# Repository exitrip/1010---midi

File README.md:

# 1010---midi
Trying organize an otherwise un-organized repo for public consumption:

## Overview
This repo contains everything one needs to repurpose an "iTrip 1G Nano" as a generic radio transmitter, including an adaptor circuit board to simplify the hack, and a "headless" Arduino program to flash firmware on to the iTrip's LPC936 microcontroller.

See the `kicad` directory for a partial schematic of the iTrip and the complete schematic and layout of the adaptor PCB.  I've got lots of the PCBs, so please ask me to send you some instead of making your own for now.

### Required supplies
If you want to replicate this work you'll need:
- iTrips (again ask me for some, I've got hundreds).  It's good to have plenty of extras for a workshop.
- an Arduino and homemade programming cable
- Soldering equipment, wire cutters, a small screw driver helps, etc.
- ~1m electrical wire per transmitter
- to pick a power source for the iTrip:
  - 2x AA/AAA battery pack, try finding them from surplus sites like [Goldmine Electronics](https://theelectronicgoldmine.com/products/g27885?_pos=18&_sid=e9574ebc7&_ss=r)
  - TO-92 or SOT23-5 3.3V, 100mA regulator (e.g. [L78L33ACZ](https://www.digikey.com/en/products/detail/stmicroelectronics/L78L33ACZ/1038304))
  - or the [FTDI FT232RL](https://www.digikey.com/en/products/detail/ftdi-future-technology-devices-international-ltd/FT232RL-REEL/1836385)  USB-to-UART converter with onboard regulator.  This chip is relatively fine pitch SMT TSSOP, so it will be challenging to seat without the right soldering tools and experience.  

A quick note about the FTDI chip:  Seating this chip will allow you to send and recieve MIDI (via serial) commands to the transmitter over USB, in fact each FTDI chip can drive up to 8 transmitters, but there are undocumented details as to how to set this up.  All of the PurrData patches, touchOSC setup, and most of the uVision code target custom modular hardware that is also poorly documented and out of scope of a workshop.  Even without the "onboard" FTDI, you can access all this functionality by using any [3.3V USB-Serial cable](https://www.adafruit.com/product/70) hooked up to the TX/RX on the adpator PCB. Reach out, I happy to discuss further.

Another note about firmware:  The LPC936 firmware programmed by the Arduino is stored in the Arduino firmware directly.  Recompiling new firmware unfortunately requires a licensed copy of KEIL uVision Cx51, which is thousands of dollars last I checked.  The "free" versions of uVision have a prohibitively small size limit, and cannot build the code as is.  I'm still investigating if I can strip the project enough...

### Setting up the programmer
See [README](arduino/exitrip_flash_programmer/README.md) in arduino folder.

## Steps for the hack
- Open up the iTrip.  Easiest way is to slip a flat head above the button and pry the plastic case open like an oyster.  Be a bit careful with the button though.
- Don't put too much stress on the cables inside the now opened iTrip, they can easily break off the PCB.
- Break the connectors from the front plastic shell.  This takes some practice, and there's maybe half a dozen ways to do this.  Notice that there's a seam in the front plastic around connectors, just under the FCC ID number.  Pressing the smaller plastic piece out of the front cover is easy, most of the time.  You can also just cut the front cover up too.
- Cut loose the antenna (black wire soldered, ANT2, to the board closest to the USB port, J3) and push the wire loose out the back of the black plastic

- Solder ~1m of wire to the antenna, this is now a [1/4 whip antenna](https://en.wikipedia.org/wiki/Whip_antenna) at ~75MHz. It's good to cheat it shorter than 1m, as that tunes it up the FM spectrum, but don't go longer.
- Connect the programming cable to the iTrip and Arduino.  Make sure the external power supply PCB is DISCONNECTED from the iTrip to be programmed.
- Power on or RESET the Arduino.  At boot up it will blink slowly, but when it successfully handshakes with the LPC936, the LED will start blinking faster during programming.  Wait until the LED is blinking slow again, which indicates programming is complete.  This is a good time to test the iTrip without the added power supply, as it will recieve power from the Arduino programmer directly.  The iTrip itself is working and correctly programmed if:
  - The red LED in the corner comes on solid 
  - The red LED turns on and off with a middle button press (this turns the transmitter on and off)
  - While the LED is on there's a signal (silence) on 87.9 MHz (every time the iTrip boots up the transmission freqency is reset to 87.9)
  - Pressing the up and down buttons, tunes the transmitter up and down.
- This step can be done at anytime, but once you've tested the iTrip works while connected to the Arduino, you can be sure that further problems are caused by the power supply.
  - Solder the desired power supply to the adaptor PCB (e.g. GND to battery negative, 3.3V to battery positive).  Any of the ICs will take 5V from either the 5V header on the adaptor or the USB port on the iTrip.  A useful 5V and 3.3V will come OUT of those headers too!

  ## Suggestions about workshops
  - FM radios are not as common as they used to be.  BRING SOME, otherwise there's a big sad trombone at the end of the build
  - Have an SDR reciever setup on a laptop to visualize the transmissions.  It will also double as a reciever.  These turnkey [RTL-SDR kits](https://www.rtl-sdr.com/buy-rtl-sdr-dvb-t-dongles/) are awesome for the price.

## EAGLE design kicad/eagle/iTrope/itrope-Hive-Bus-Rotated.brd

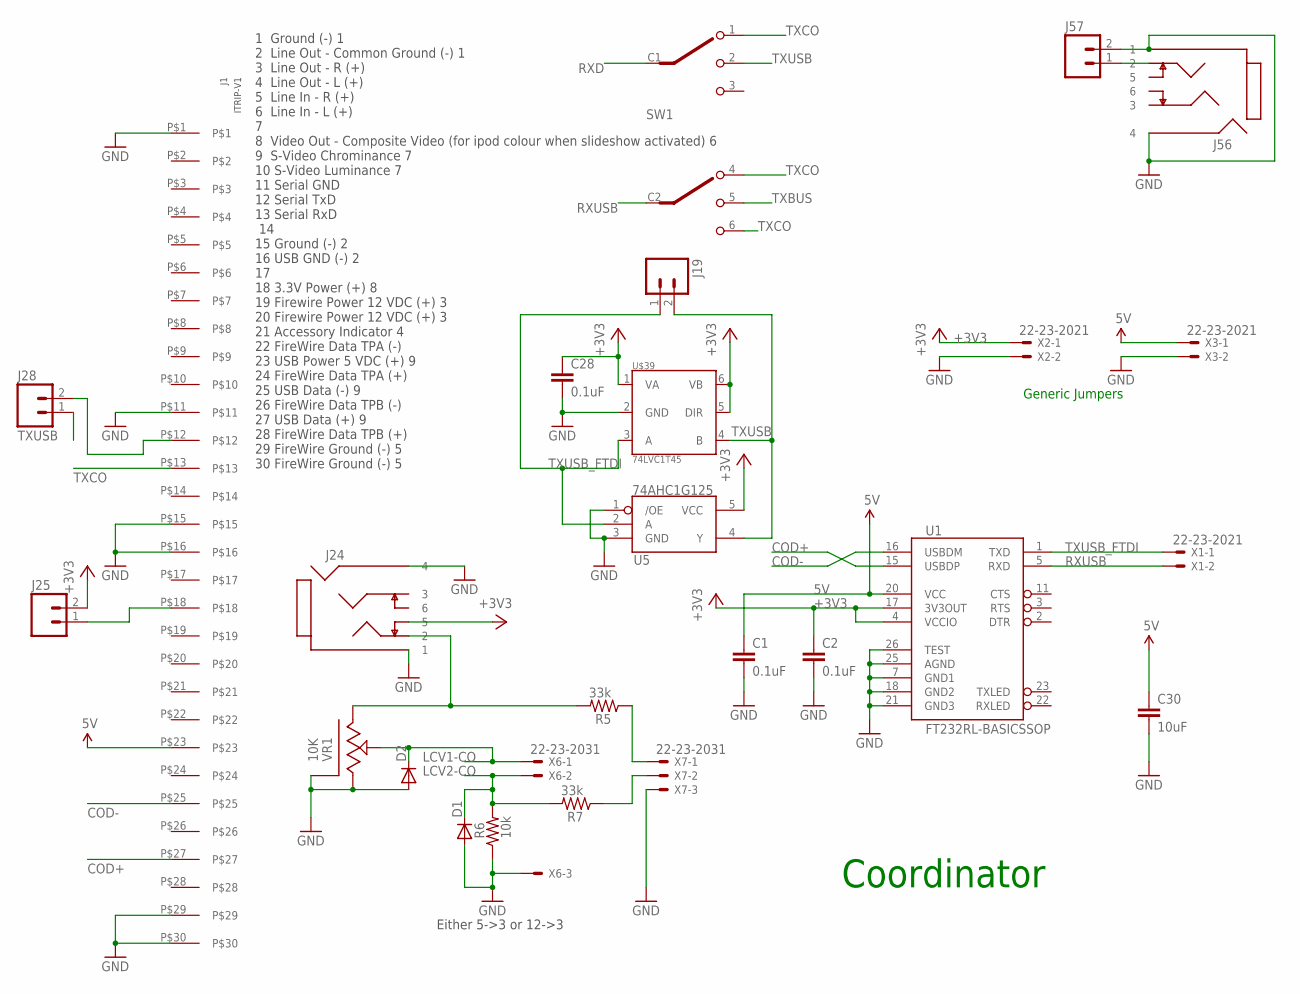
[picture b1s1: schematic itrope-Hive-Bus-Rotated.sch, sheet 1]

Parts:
C1, C2, C28: 0.1uF; CAP-0603
C30: 10uF; CAP-0805
D1, D2: DIODESOD; SOD-323
J1: ITRIP-V1; 30PINEDGE+ITRIP
J19, J25, J28, J57: HDR-2H02-PTH; H02-PTH
J24, J56: JACK-PHONO-4COND-SW; CUI-SJ-4351
R5, R7: 33k; C0402
R6: 10k; C0402
SW1: SWITCH-SLIDE-DP3TAYZ0203; SWITCH-CK-AYZ0203
U1: FT232RL-BASICSSOP; SSOP28DB
U5: 74AHC1G125; SOT23-5
U$39: 74LVC1T45; SC70-6
VR1: 10K; POT-SLIDE-30MM
X1, X2, X3: 22-23-2021
X6, X7: 22-23-2031

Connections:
5V: C1.1, C30.1, J1.P$23, U1.20 (VCC), X3.1; also elsewhere on the board
+3V3: C2.1, C28.1, J24.5, J25.2, U1.4 (VCCIO), U1.17 (3V3OUT), U5.5 (VCC), U$39.1 (VA), U$39.5 (DIR), U$39.6 (VB), X2.1; also elsewhere on the board
COD+: J1.P$27, U1.15 (USBDP)
COD-: J1.P$25, U1.16 (USBDM)
GND: C1.2, C2.2, C28.2, C30.2, D1.2 (A), D2.2 (A), J1.P$1, J1.P$11, J1.P$15, J1.P$16, J1.P$29, J1.P$30, J24.1, J24.4, J56.1, J56.4, J57.2, R6.1, U1.7 (GND1), U1.18 (GND2), U1.21 (GND3), U1.25 (AGND), U1.26 (TEST), U5.1 (/OE), U5.3 (GND), U$39.2 (GND), VR1.3, VR1.P$4 (CASE), VR1.P$5 (CASE), VR1.P$6 (CASE), VR1.P$7 (CASE), X2.2, X3.2, X6.3, X7.3; also elsewhere on the board
LCV1-CO: D2.1 (C), VR1.2, X6.1
LCV2-CO: D1.1 (C), R6.2, R7.2, X6.2
unnamed: R7.1, X7.2
unnamed: R5.1, X7.1
unnamed: J1.P$18, J25.1
unnamed: J24.2, R5.2, VR1.1
unnamed: J1.P$12, J28.2
unnamed: J56.2, J57.1
RXD: SW1.C1; also elsewhere on the board
RXUSB: SW1.C2, U1.5 (RXD), X1.2
TXBUS: SW1.5; also elsewhere on the board
TXCO: J1.P$13, SW1.1, SW1.4, SW1.6
TXUSB: J19.2, J28.1, SW1.2, U5.4 (Y), U$39.4 (B)
TXUSB_FTDI: J19.1, U1.1 (TXD), U5.2 (A), U$39.3 (A), X1.1

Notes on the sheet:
1 Ground (-) 1 2 Line Out - Common Ground (-) 1 3 Line Out - R (+) 4 Line Out - L (+) 5 Line In - R (+) 6 Line In - L (+) 7 8 Video Out - Composite Video (for ipod colour when slideshow activated) 6 9 S-Video Chrominance 7 10 S-Video Luminance 7 11 Serial GND 12 Serial TxD 13 Serial RxD 14 15 Groun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
Either 5->3 or 12->3
Generic Jumpers
Coordinator

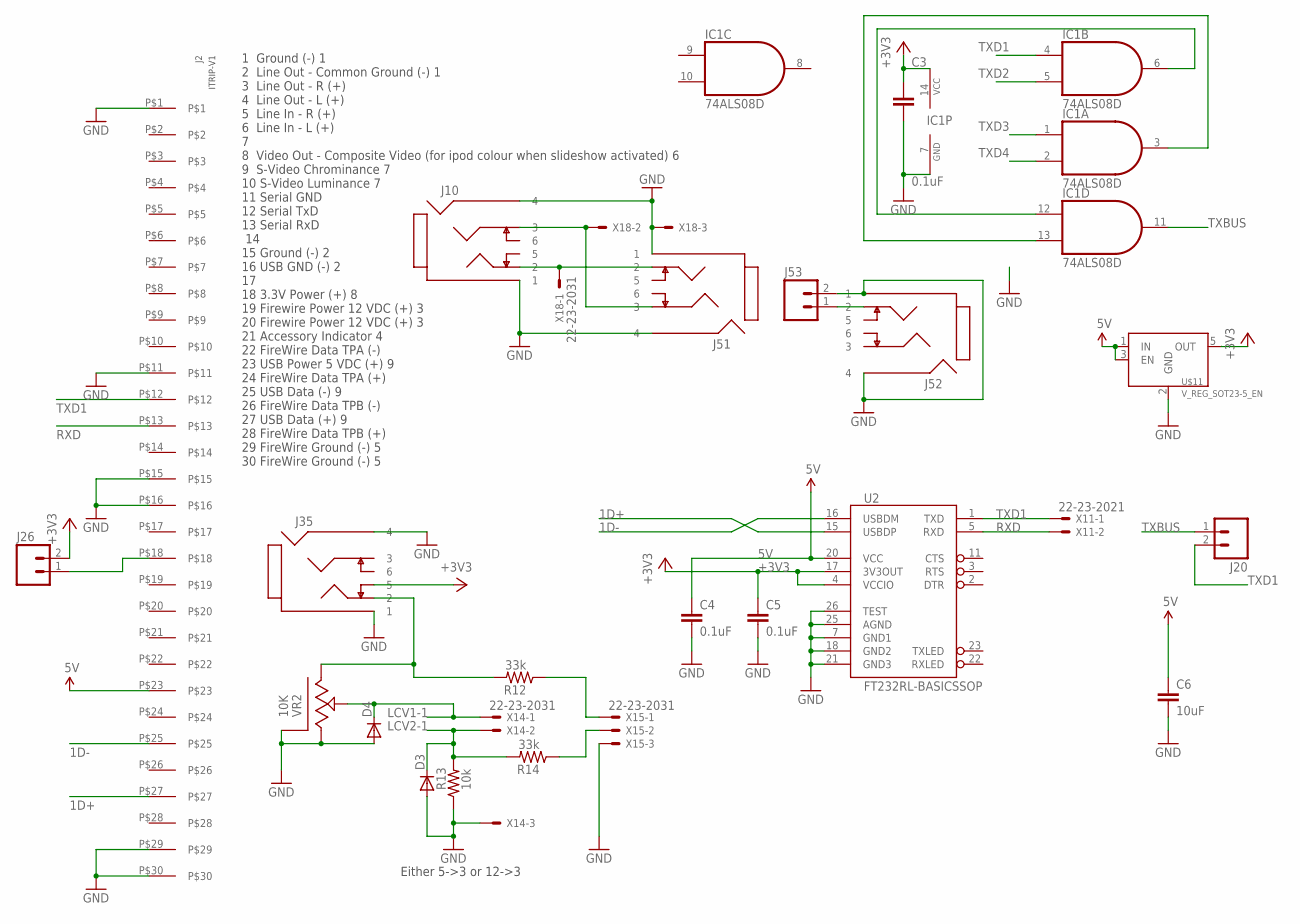
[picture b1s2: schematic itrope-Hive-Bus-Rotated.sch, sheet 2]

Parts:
C3, C4, C5: 0.1uF; CAP-0603
C6: 10uF; CAP-0805
D3, D4: DIODESOD; SOD-323
IC1: 74ALS08D; SO14
J2: ITRIP-V1; 30PINEDGE+ITRIP
J10, J35, J51, J52: JACK-PHONO-4COND-SW; CUI-SJ-4351
J20, J26, J53: HDR-2H02-PTH; H02-PTH
R12, R14: 33k; C0402
R13: 10k; C0402
U2: FT232RL-BASICSSOP; SSOP28DB
U$11: V_REG_SOT23-5_EN; SOT23-5
VR2: 10K; POT-SLIDE-30MM
X11: 22-23-2021
X14, X15, X18: 22-23-2031

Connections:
1D+: J2.P$27, U2.15 (USBDP)
1D-: J2.P$25, U2.16 (USBDM)
5V: C4.1, C6.1, J2.P$23, U2.20 (VCC), U$11.1 (IN), U$11.3 (EN); also elsewhere on the board
+3V3: C3.1, C5.1, IC1.14 (VCC), J26.2, J35.5, U2.4 (VCCIO), U2.17 (3V3OUT), U$11.5 (OUT); also elsewhere on the board
GND: C3.2, C4.2, C5.2, C6.2, D3.2 (A), D4.2 (A), IC1.7 (GND), J2.P$1, J2.P$11, J2.P$15, J2.P$16, J2.P$29, J2.P$30, J10.1, J10.4, J35.1, J35.4, J51.1, J51.4, J52.1, J52.4, J53.2, R13.1, U2.7 (GND1), U2.18 (GND2), U2.21 (GND3), U2.25 (AGND), U2.26 (TEST), U$11.2 (GND), VR2.3, VR2.P$4 (CASE), VR2.P$5 (CASE), VR2.P$6 (CASE), VR2.P$7 (CASE), X14.3, X15.3, X18.3; also elsewhere on the board
LCV1-1: D4.1 (C), VR2.2, X14.1
LCV2-1: D3.1 (C), R13.2, R14.2, X14.2
unnamed: R14.1, X15.2
unnamed: R12.1, X15.1
unnamed: J2.P$18, J26.1
unnamed: IC1.6 (O), IC1.12 (I0)
unnamed: IC1.3 (O), IC1.13 (I1)
unnamed: J35.2, R12.2, VR2.1
unnamed: J10.2, J51.2, X18.1
unnamed: J10.3, J51.3, X18.2
unnamed: J52.2, J53.1
RXD: J2.P$13, U2.5 (RXD), X11.2; also elsewhere on the board
TXBUS: IC1.11 (O), J20.1; also elsewhere on the board
TXD1: IC1.4 (I0), J2.P$12, J20.2, U2.1 (TXD), X11.1; also elsewhere on the board
TXD2: IC1.5 (I1); also elsewhere on the board
TXD3: IC1.1 (I0); also elsewhere on the board
TXD4: IC1.2 (I1); also elsewhere on the board

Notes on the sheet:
1 Ground (-) 1 2 Line Out - Common Ground (-) 1 3 Line Out - R (+) 4 Line Out - L (+) 5 Line In - R (+) 6 Line In - L (+) 7 8 Video Out - Composite Video (for ipod colour when slideshow activated) 6 9 S-Video Chrominance 7 10 S-Video Luminance 7 11 Serial GND 12 Serial TxD 13 Serial RxD 14 15 Groun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
Either 5->3 or 12->3

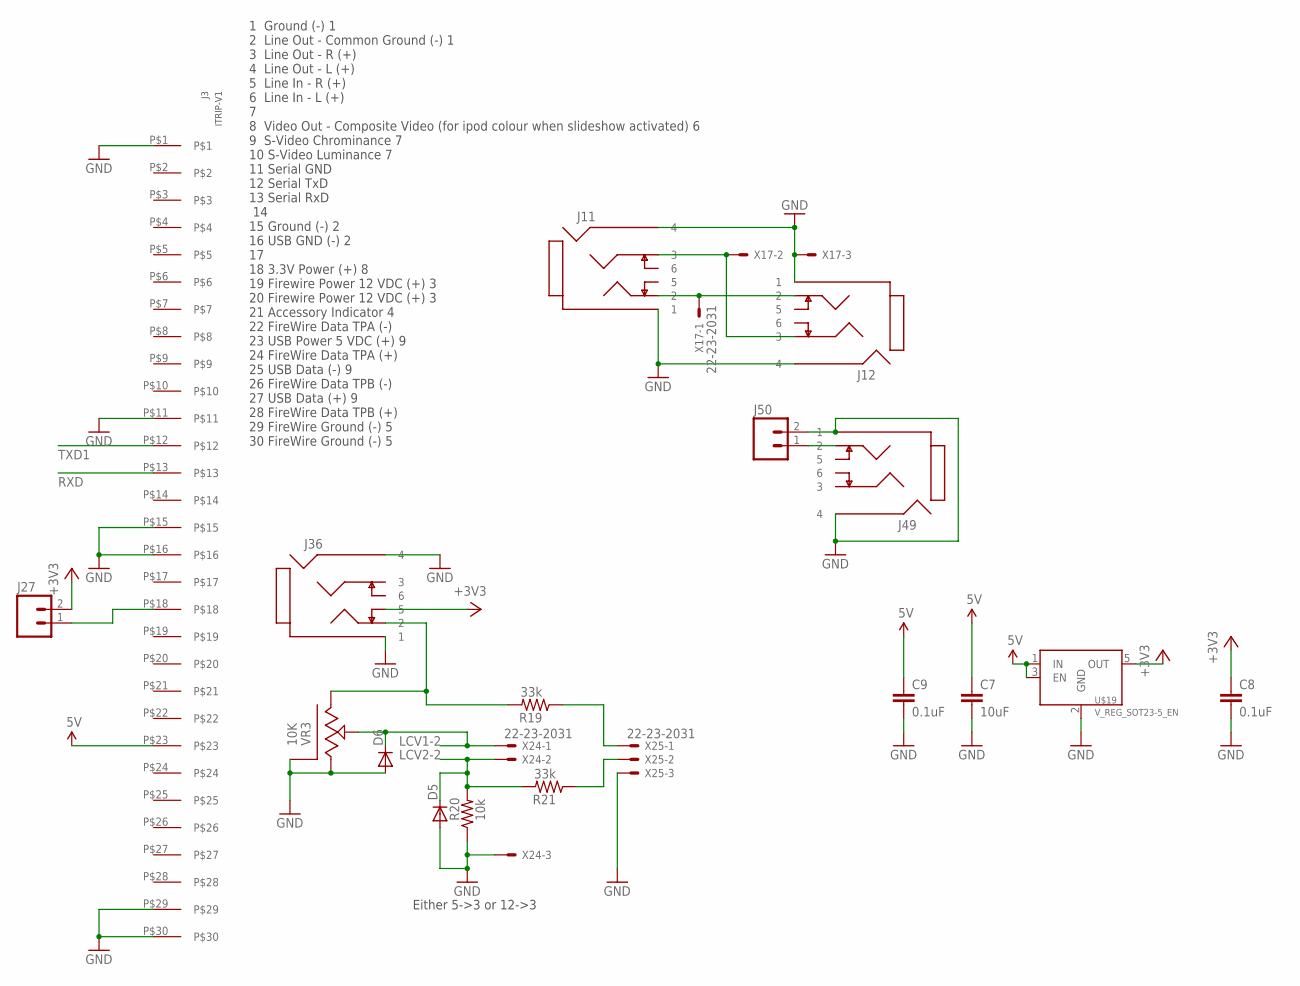
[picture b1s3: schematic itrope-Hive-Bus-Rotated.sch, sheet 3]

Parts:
C7: 10uF; CAP-0805
C8, C9: 0.1uF; CAP-0603
D5, D6: DIODESOD; SOD-323
J3: ITRIP-V1; 30PINEDGE+ITRIP
J11, J12, J36, J49: JACK-PHONO-4COND-SW; CUI-SJ-4351
J27, J50: HDR-2H02-PTH; H02-PTH
R19, R21: 33k; C0402
R20: 10k; C0402
U$19: V_REG_SOT23-5_EN; SOT23-5
VR3: 10K; POT-SLIDE-30MM
X17, X24, X25: 22-23-2031

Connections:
5V: C7.1, C9.1, J3.P$23, U$19.1 (IN), U$19.3 (EN); also elsewhere on the board
+3V3: C8.1, J27.2, J36.5, U$19.5 (OUT); also elsewhere on the board
GND: C7.2, C8.2, C9.2, D5.2 (A), D6.2 (A), J3.P$1, J3.P$11, J3.P$15, J3.P$16, J3.P$29, J3.P$30, J11.1, J11.4, J12.1, J12.4, J36.1, J36.4, J49.1, J49.4, J50.2, R20.1, U$19.2 (GND), VR3.3, VR3.P$4 (CASE), VR3.P$5 (CASE), VR3.P$6 (CASE), VR3.P$7 (CASE), X17.3, X24.3, X25.3; also elsewhere on the board
LCV1-2: D6.1 (C), VR3.2, X24.1
LCV2-2: D5.1 (C), R20.2, R21.2, X24.2
unnamed: J3.P$18, J27.1
unnamed: R21.1, X25.2
unnamed: R19.1, X25.1
unnamed: J36.2, R19.2, VR3.1
unnamed: J11.2, J12.2, X17.1
unnamed: J11.3, J12.3, X17.2
unnamed: J49.2, J50.1
RXD: J3.P$13; also elsewhere on the board
TXD1: J3.P$12; also elsewhere on the board

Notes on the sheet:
1 Ground (-) 1 2 Line Out - Common Ground (-) 1 3 Line Out - R (+) 4 Line Out - L (+) 5 Line In - R (+) 6 Line In - L (+) 7 8 Video Out - Composite Video (for ipod colour when slideshow activated) 6 9 S-Video Chrominance 7 10 S-Video Luminance 7 11 Serial GND 12 Serial TxD 13 Serial RxD 14 15 Groun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
Either 5->3 or 12->3

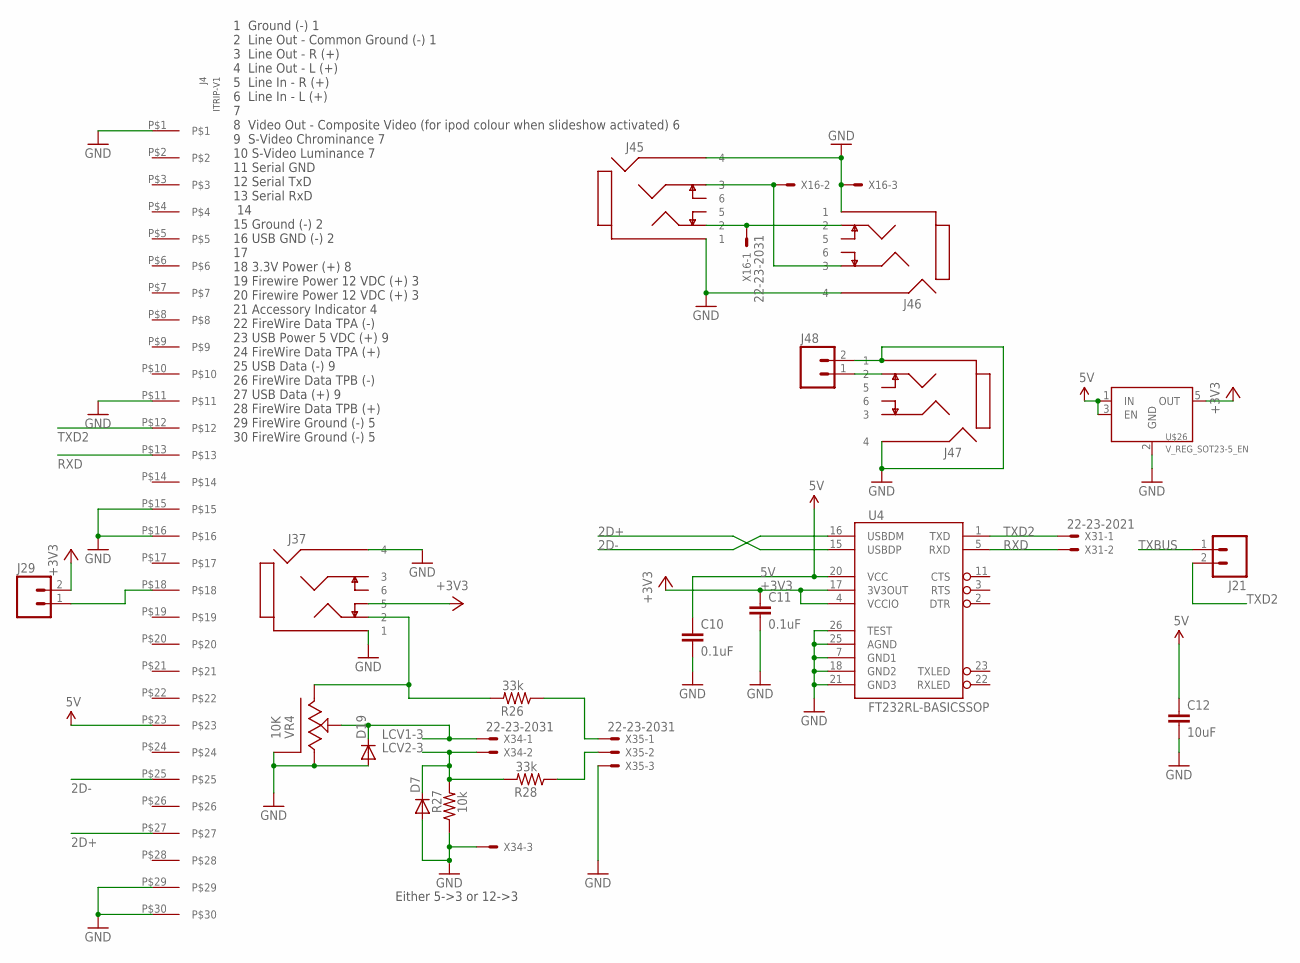
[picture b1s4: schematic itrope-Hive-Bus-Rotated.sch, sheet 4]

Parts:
C10, C11: 0.1uF; CAP-0603
C12: 10uF; CAP-0805
D7, D19: DIODESOD; SOD-323
J4: ITRIP-V1; 30PINEDGE+ITRIP
J21, J29, J48: HDR-2H02-PTH; H02-PTH
J37, J45, J46, J47: JACK-PHONO-4COND-SW; CUI-SJ-4351
R26, R28: 33k; C0402
R27: 10k; C0402
U4: FT232RL-BASICSSOP; SSOP28DB
U$26: V_REG_SOT23-5_EN; SOT23-5
VR4: 10K; POT-SLIDE-30MM
X16, X34, X35: 22-23-2031
X31: 22-23-2021

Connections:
2D+: J4.P$27, U4.15 (USBDP)
2D-: J4.P$25, U4.16 (USBDM)
5V: C10.1, C12.1, J4.P$23, U4.20 (VCC), U$26.1 (IN), U$26.3 (EN); also elsewhere on the board
+3V3: C11.1, J29.2, J37.5, U4.4 (VCCIO), U4.17 (3V3OUT), U$26.5 (OUT); also elsewhere on the board
GND: C10.2, C11.2, C12.2, D7.2 (A), D19.2 (A), J4.P$1, J4.P$11, J4.P$15, J4.P$16, J4.P$29, J4.P$30, J37.1, J37.4, J45.1, J45.4, J46.1, J46.4, J47.1, J47.4, J48.2, R27.1, U4.7 (GND1), U4.18 (GND2), U4.21 (GND3), U4.25 (AGND), U4.26 (TEST), U$26.2 (GND), VR4.3, VR4.P$4 (CASE), VR4.P$5 (CASE), VR4.P$6 (CASE), VR4.P$7 (CASE), X16.3, X34.3, X35.3; also elsewhere on the board
LCV1-3: D19.1 (C), VR4.2, X34.1
LCV2-3: D7.1 (C), R27.2, R28.2, X34.2
unnamed: J4.P$18, J29.1
unnamed: R28.1, X35.2
unnamed: R26.1, X35.1
unnamed: J37.2, R26.2, VR4.1
unnamed: J45.2, J46.2, X16.1
unnamed: J45.3, J46.3, X16.2
unnamed: J47.2, J48.1
RXD: J4.P$13, U4.5 (RXD), X31.2; also elsewhere on the board
TXBUS: J21.1; also elsewhere on the board
TXD2: J4.P$12, J21.2, U4.1 (TXD), X31.1; also elsewhere on the board

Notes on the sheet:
1 Ground (-) 1 2 Line Out - Common Ground (-) 1 3 Line Out - R (+) 4 Line Out - L (+) 5 Line In - R (+) 6 Line In - L (+) 7 8 Video Out - Composite Video (for ipod colour when slideshow activated) 6 9 S-Video Chrominance 7 10 S-Video Luminance 7 11 Serial GND 12 Serial TxD 13 Serial RxD 14 15 Groun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
Either 5->3 or 12->3

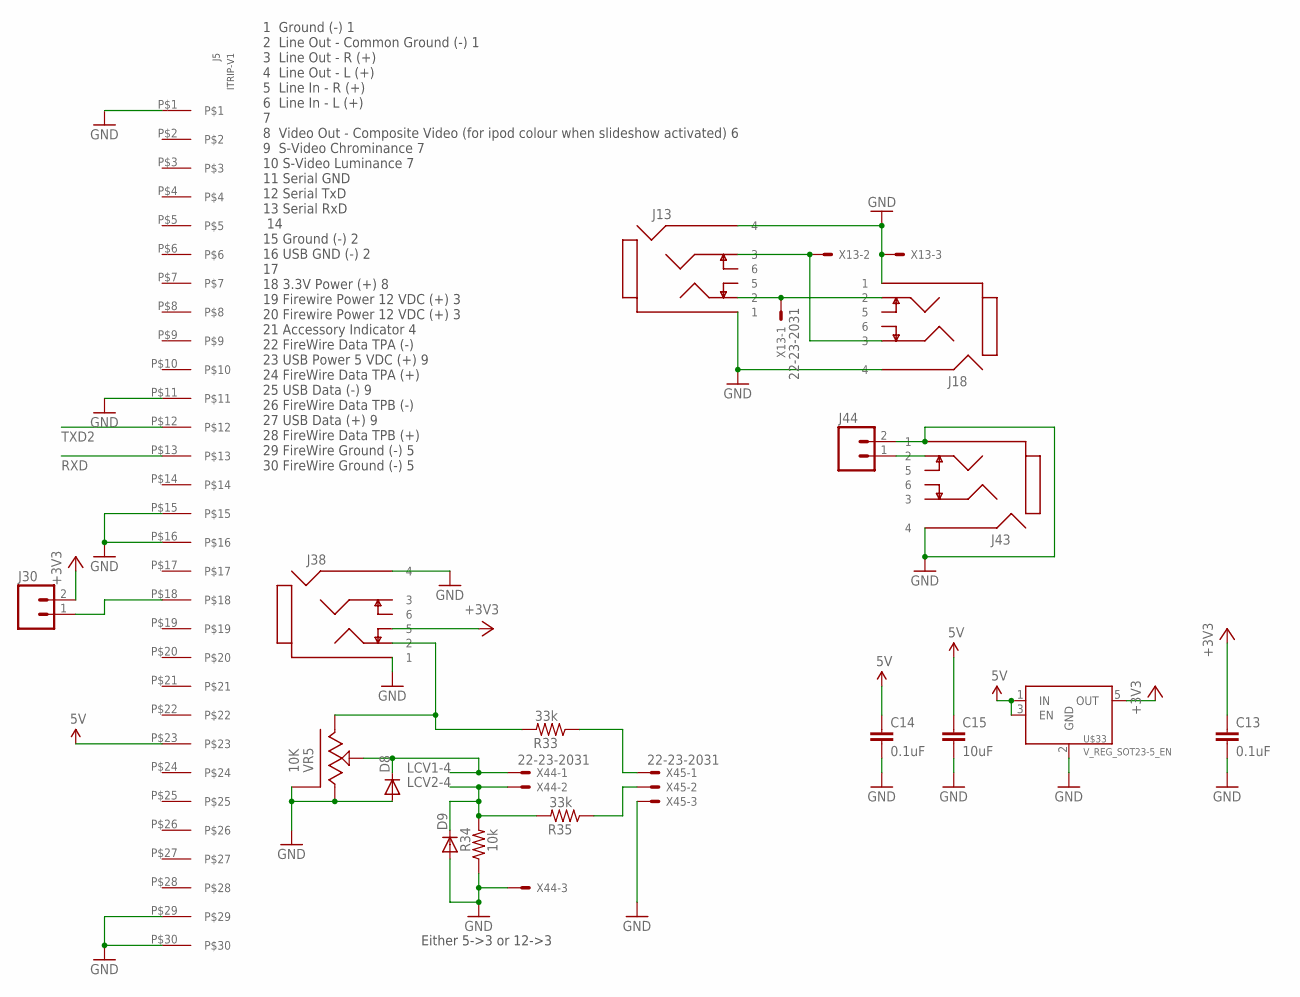
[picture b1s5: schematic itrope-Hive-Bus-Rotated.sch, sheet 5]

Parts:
C13, C14: 0.1uF; CAP-0603
C15: 10uF; CAP-0805
D8, D9: DIODESOD; SOD-323
J5: ITRIP-V1; 30PINEDGE+ITRIP
J13, J18, J38, J43: JACK-PHONO-4COND-SW; CUI-SJ-4351
J30, J44: HDR-2H02-PTH; H02-PTH
R33, R35: 33k; C0402
R34: 10k; C0402
U$33: V_REG_SOT23-5_EN; SOT23-5
VR5: 10K; POT-SLIDE-30MM
X13, X44, X45: 22-23-2031

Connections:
5V: C14.1, C15.1, J5.P$23, U$33.1 (IN), U$33.3 (EN); also elsewhere on the board
+3V3: C13.1, J30.2, J38.5, U$33.5 (OUT); also elsewhere on the board
GND: C13.2, C14.2, C15.2, D8.2 (A), D9.2 (A), J5.P$1, J5.P$11, J5.P$15, J5.P$16, J5.P$29, J5.P$30, J13.1, J13.4, J18.1, J18.4, J38.1, J38.4, J43.1, J43.4, J44.2, R34.1, U$33.2 (GND), VR5.3, VR5.P$4 (CASE), VR5.P$5 (CASE), VR5.P$6 (CASE), VR5.P$7 (CASE), X13.3, X44.3, X45.3; also elsewhere on the board
LCV1-4: D8.1 (C), VR5.2, X44.1
LCV2-4: D9.1 (C), R34.2, R35.2, X44.2
unnamed: J5.P$18, J30.1
unnamed: R35.1, X45.2
unnamed: R33.1, X45.1
unnamed: J38.2, R33.2, VR5.1
unnamed: J13.2, J18.2, X13.1
unnamed: J13.3, J18.3, X13.2
unnamed: J43.2, J44.1
RXD: J5.P$13; also elsewhere on the board
TXD2: J5.P$12; also elsewhere on the board

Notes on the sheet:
1 Ground (-) 1 2 Line Out - Common Ground (-) 1 3 Line Out - R (+) 4 Line Out - L (+) 5 Line In - R (+) 6 Line In - L (+) 7 8 Video Out - Composite Video (for ipod colour when slideshow activated) 6 9 S-Video Chrominance 7 10 S-Video Luminance 7 11 Serial GND 12 Serial TxD 13 Serial RxD 14 15 Groun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
Either 5->3 or 12->3

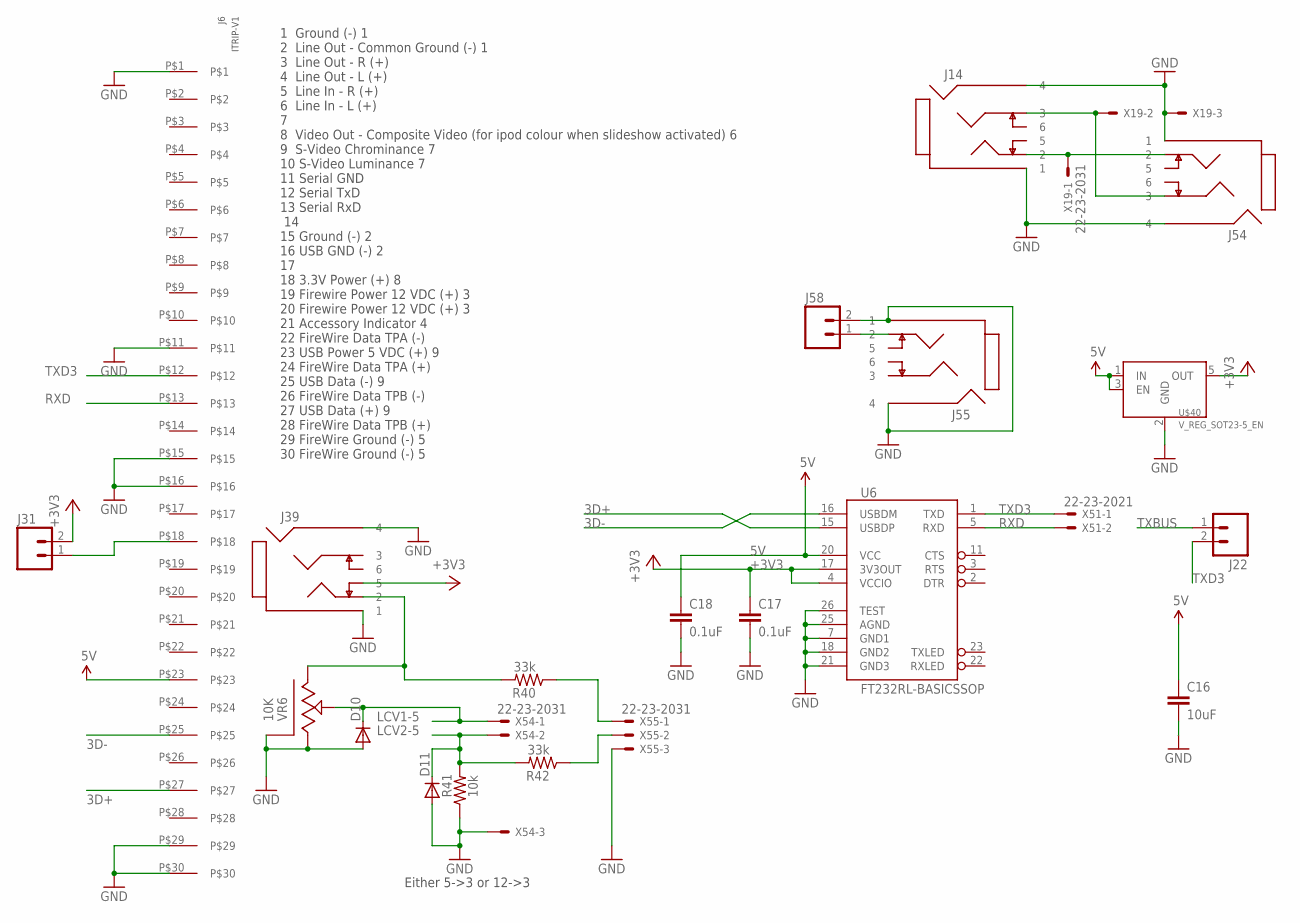
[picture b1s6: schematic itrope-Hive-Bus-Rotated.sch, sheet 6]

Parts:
C16: 10uF; CAP-0805
C17, C18: 0.1uF; CAP-0603
D10, D11: DIODESOD; SOD-323
J6: ITRIP-V1; 30PINEDGE+ITRIP
J14, J39, J54, J55: JACK-PHONO-4COND-SW; CUI-SJ-4351
J22, J31, J58: HDR-2H02-PTH; H02-PTH
R40, R42: 33k; C0402
R41: 10k; C0402
U6: FT232RL-BASICSSOP; SSOP28DB
U$40: V_REG_SOT23-5_EN; SOT23-5
VR6: 10K; POT-SLIDE-30MM
X19, X54, X55: 22-23-2031
X51: 22-23-2021

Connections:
3D+: J6.P$27, U6.15 (USBDP)
3D-: J6.P$25, U6.16 (USBDM)
5V: C16.1, C18.1, J6.P$23, U6.20 (VCC), U$40.1 (IN), U$40.3 (EN); also elsewhere on the board
+3V3: C17.1, J31.2, J39.5, U6.4 (VCCIO), U6.17 (3V3OUT), U$40.5 (OUT); also elsewhere on the board
GND: C16.2, C17.2, C18.2, D10.2 (A), D11.2 (A), J6.P$1, J6.P$11, J6.P$15, J6.P$16, J6.P$29, J6.P$30, J14.1, J14.4, J39.1, J39.4, J54.1, J54.4, J55.1, J55.4, J58.2, R41.1, U6.7 (GND1), U6.18 (GND2), U6.21 (GND3), U6.25 (AGND), U6.26 (TEST), U$40.2 (GND), VR6.3, VR6.P$4 (CASE), VR6.P$5 (CASE), VR6.P$6 (CASE), VR6.P$7 (CASE), X19.3, X54.3, X55.3; also elsewhere on the board
LCV1-5: D10.1 (C), VR6.2, X54.1
LCV2-5: D11.1 (C), R41.2, R42.2, X54.2
unnamed: J6.P$18, J31.1
unnamed: R42.1, X55.2
unnamed: R40.1, X55.1
unnamed: J39.2, R40.2, VR6.1
unnamed: J14.2, J54.2, X19.1
unnamed: J14.3, J54.3, X19.2
unnamed: J55.2, J58.1
RXD: J6.P$13, U6.5 (RXD), X51.2; also elsewhere on the board
TXBUS: J22.1; also elsewhere on the board
TXD3: J6.P$12, J22.2, U6.1 (TXD), X51.1; also elsewhere on the board

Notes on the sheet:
1 Ground (-) 1 2 Line Out - Common Ground (-) 1 3 Line Out - R (+) 4 Line Out - L (+) 5 Line In - R (+) 6 Line In - L (+) 7 8 Video Out - Composite Video (for ipod colour when slideshow activated) 6 9 S-Video Chrominance 7 10 S-Video Luminance 7 11 Serial GND 12 Serial TxD 13 Serial RxD 14 15 Groun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
Either 5->3 or 12->3

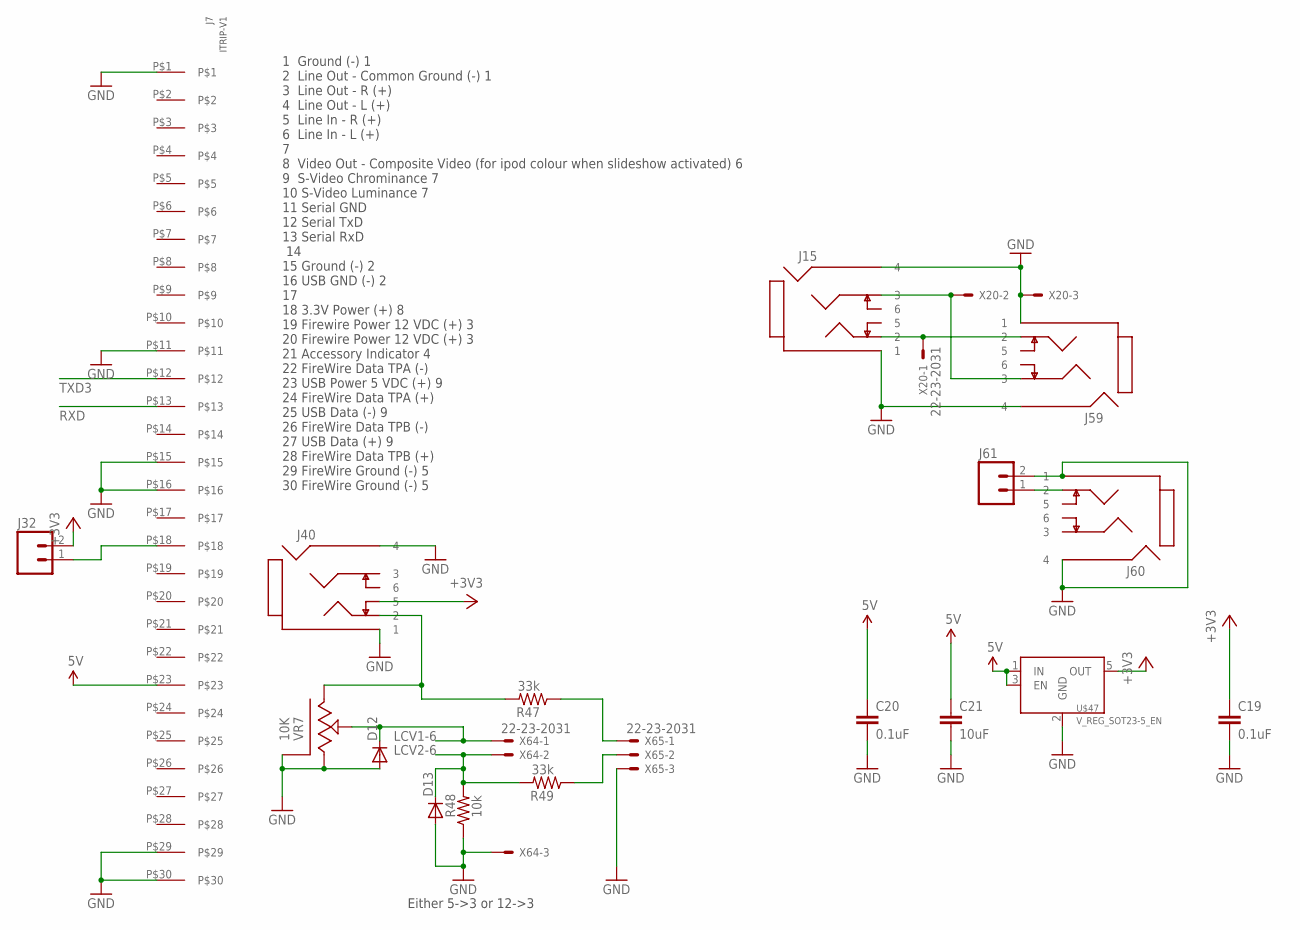
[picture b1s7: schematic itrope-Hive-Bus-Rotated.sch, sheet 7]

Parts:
C19, C20: 0.1uF; CAP-0603
C21: 10uF; CAP-0805
D12, D13: DIODESOD; SOD-323
J7: ITRIP-V1; 30PINEDGE+ITRIP
J15, J40, J59, J60: JACK-PHONO-4COND-SW; CUI-SJ-4351
J32, J61: HDR-2H02-PTH; H02-PTH
R47, R49: 33k; C0402
R48: 10k; C0402
U$47: V_REG_SOT23-5_EN; SOT23-5
VR7: 10K; POT-SLIDE-30MM
X20, X64, X65: 22-23-2031

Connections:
5V: C20.1, C21.1, J7.P$23, U$47.1 (IN), U$47.3 (EN); also elsewhere on the board
+3V3: C19.1, J32.2, J40.5, U$47.5 (OUT); also elsewhere on the board
GND: C19.2, C20.2, C21.2, D12.2 (A), D13.2 (A), J7.P$1, J7.P$11, J7.P$15, J7.P$16, J7.P$29, J7.P$30, J15.1, J15.4, J40.1, J40.4, J59.1, J59.4, J60.1, J60.4, J61.2, R48.1, U$47.2 (GND), VR7.3, VR7.P$4 (CASE), VR7.P$5 (CASE), VR7.P$6 (CASE), VR7.P$7 (CASE), X20.3, X64.3, X65.3; also elsewhere on the board
LCV1-6: D12.1 (C), VR7.2, X64.1
LCV2-6: D13.1 (C), R48.2, R49.2, X64.2
unnamed: J7.P$18, J32.1
unnamed: R49.1, X65.2
unnamed: R47.1, X65.1
unnamed: J40.2, R47.2, VR7.1
unnamed: J15.2, J59.2, X20.1
unnamed: J15.3, J59.3, X20.2
unnamed: J60.2, J61.1
RXD: J7.P$13; also elsewhere on the board
TXD3: J7.P$12; also elsewhere on the board

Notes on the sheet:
1 Ground (-) 1 2 Line Out - Common Ground (-) 1 3 Line Out - R (+) 4 Line Out - L (+) 5 Line In - R (+) 6 Line In - L (+) 7 8 Video Out - Composite Video (for ipod colour when slideshow activated) 6 9 S-Video Chrominance 7 10 S-Video Luminance 7 11 Serial GND 12 Serial TxD 13 Serial RxD 14 15 Groun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
Either 5->3 or 12->3

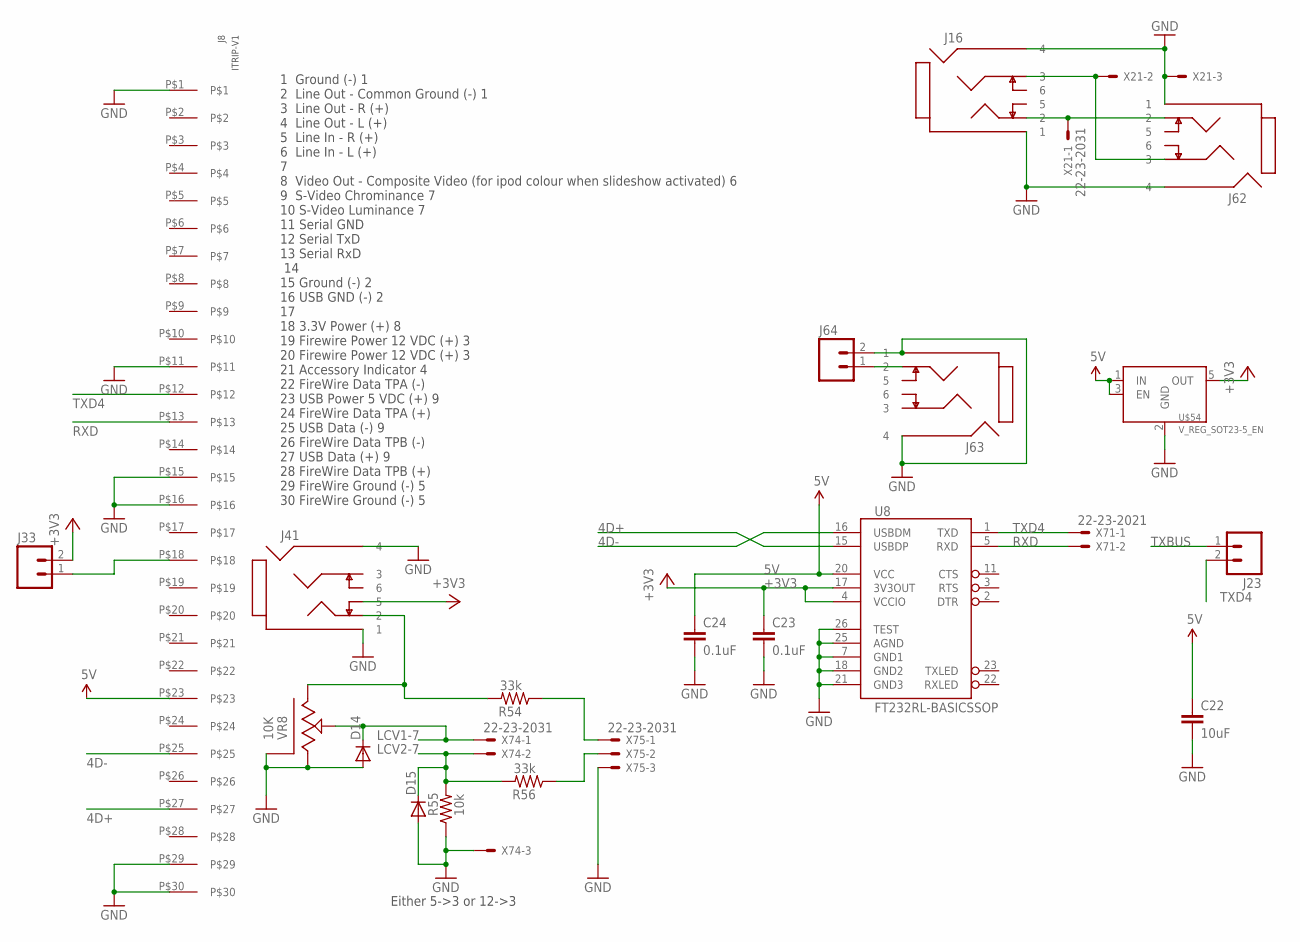
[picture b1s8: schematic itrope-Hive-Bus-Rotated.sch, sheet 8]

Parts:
C22: 10uF; CAP-0805
C23, C24: 0.1uF; CAP-0603
D14, D15: DIODESOD; SOD-323
J8: ITRIP-V1; 30PINEDGE+ITRIP
J16, J41, J62, J63: JACK-PHONO-4COND-SW; CUI-SJ-4351
J23, J33, J64: HDR-2H02-PTH; H02-PTH
R54, R56: 33k; C0402
R55: 10k; C0402
U8: FT232RL-BASICSSOP; SSOP28DB
U$54: V_REG_SOT23-5_EN; SOT23-5
VR8: 10K; POT-SLIDE-30MM
X21, X74, X75: 22-23-2031
X71: 22-23-2021

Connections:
4D+: J8.P$27, U8.15 (USBDP)
4D-: J8.P$25, U8.16 (USBDM)
5V: C22.1, C24.1, J8.P$23, U8.20 (VCC), U$54.1 (IN), U$54.3 (EN); also elsewhere on the board
+3V3: C23.1, J33.2, J41.5, U8.4 (VCCIO), U8.17 (3V3OUT), U$54.5 (OUT); also elsewhere on the board
GND: C22.2, C23.2, C24.2, D14.2 (A), D15.2 (A), J8.P$1, J8.P$11, J8.P$15, J8.P$16, J8.P$29, J8.P$30, J16.1, J16.4, J41.1, J41.4, J62.1, J62.4, J63.1, J63.4, J64.2, R55.1, U8.7 (GND1), U8.18 (GND2), U8.21 (GND3), U8.25 (AGND), U8.26 (TEST), U$54.2 (GND), VR8.3, VR8.P$4 (CASE), VR8.P$5 (CASE), VR8.P$6 (CASE), VR8.P$7 (CASE), X21.3, X74.3, X75.3; also elsewhere on the board
LCV1-7: D14.1 (C), VR8.2, X74.1
LCV2-7: D15.1 (C), R55.2, R56.2, X74.2
unnamed: J8.P$18, J33.1
unnamed: R56.1, X75.2
unnamed: R54.1, X75.1
unnamed: J41.2, R54.2, VR8.1
unnamed: J16.2, J62.2, X21.1
unnamed: J16.3, J62.3, X21.2
unnamed: J63.2, J64.1
RXD: J8.P$13, U8.5 (RXD), X71.2; also elsewhere on the board
TXBUS: J23.1; also elsewhere on the board
TXD4: J8.P$12, J23.2, U8.1 (TXD), X71.1; also elsewhere on the board

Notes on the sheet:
1 Ground (-) 1 2 Line Out - Common Ground (-) 1 3 Line Out - R (+) 4 Line Out - L (+) 5 Line In - R (+) 6 Line In - L (+) 7 8 Video Out - Composite Video (for ipod colour when slideshow activated) 6 9 S-Video Chrominance 7 10 S-Video Luminance 7 11 Serial GND 12 Serial TxD 13 Serial RxD 14 15 Groun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
Either 5->3 or 12->3

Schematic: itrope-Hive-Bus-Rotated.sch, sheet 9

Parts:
C25, C26: 0.1uF; CAP-0603
C27: 10uF; CAP-0805
D16, D17: DIODESOD; SOD-323
J9: ITRIP-V1; 30PINEDGE+ITRIP
J17, J42, J65, J66: JACK-PHONO-4COND-SW; CUI-SJ-4351
J34, J67: HDR-2H02-PTH; H02-PTH
R61, R63: 33k; C0402
R62: 10k; C0402
U$61: V_REG_SOT23-5_EN; SOT23-5
VR9: 10K; POT-SLIDE-30MM
X22, X84, X85: 22-23-2031

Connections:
5V: C26.1, C27.1, J9.P$23, U$61.1 (IN), U$61.3 (EN); also elsewhere on the board
+3V3: C25.1, J34.2, J42.5, U$61.5 (OUT); also elsewhere on the board
GND: C25.2, C26.2, C27.2, D16.2 (A), D17.2 (A), J9.P$1, J9.P$11, J9.P$15, J9.P$16, J9.P$29, J9.P$30, J17.1, J17.4, J42.1, J42.4, J65.1, J65.4, J66.1, J66.4, J67.2, R62.1, U$61.2 (GND), VR9.3, VR9.P$4 (CASE), VR9.P$5 (CASE), VR9.P$6 (CASE), VR9.P$7 (CASE), X22.3, X84.3, X85.3; also elsewhere on the board
LCV1-8: D16.1 (C), VR9.2, X84.1
LCV2-8: D17.1 (C), R62.2, R63.2, X84.2
unnamed: J9.P$18, J34.1
unnamed: R63.1, X85.2
unnamed: R61.1, X85.1
unnamed: J42.2, R61.2, VR9.1
unnamed: J17.2, J65.2, X22.1
unnamed: J17.3, J65.3, X22.2
unnamed: J66.2, J67.1
RXD: J9.P$13; also elsewhere on the board
TXD4: J9.P$12; also elsewhere on the board

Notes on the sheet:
1 Ground (-) 1 2 Line Out - Common Ground (-) 1 3 Line Out - R (+) 4 Line Out - L (+) 5 Line In - R (+) 6 Line In - L (+) 7 8 Video Out - Composite Video (for ipod colour when slideshow activated) 6 9 S-Video Chrominance 7 10 S-Video Luminance 7 11 Serial GND 12 Serial TxD 13 Serial RxD 14 15 Groun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
Either 5->3 or 12->3

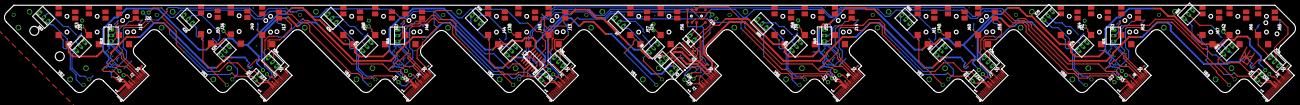
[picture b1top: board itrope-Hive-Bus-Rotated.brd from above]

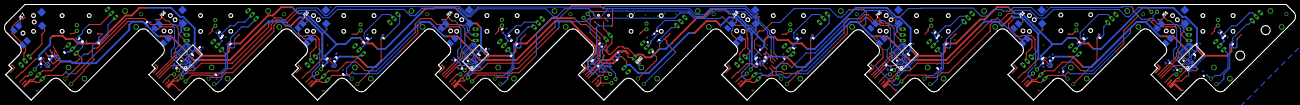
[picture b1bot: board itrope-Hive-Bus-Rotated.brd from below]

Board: 2 copper layers, 573.8 x 42.5 mm, 200 parts (96 on the bottom side), 105 nets.

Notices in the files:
parts and their libraries:
SparkFun: Released under the Creative Commons Attribution Share-Alike 3.0 License
SparkFun: http://creativecommons.org/licenses/by-sa/3.0
